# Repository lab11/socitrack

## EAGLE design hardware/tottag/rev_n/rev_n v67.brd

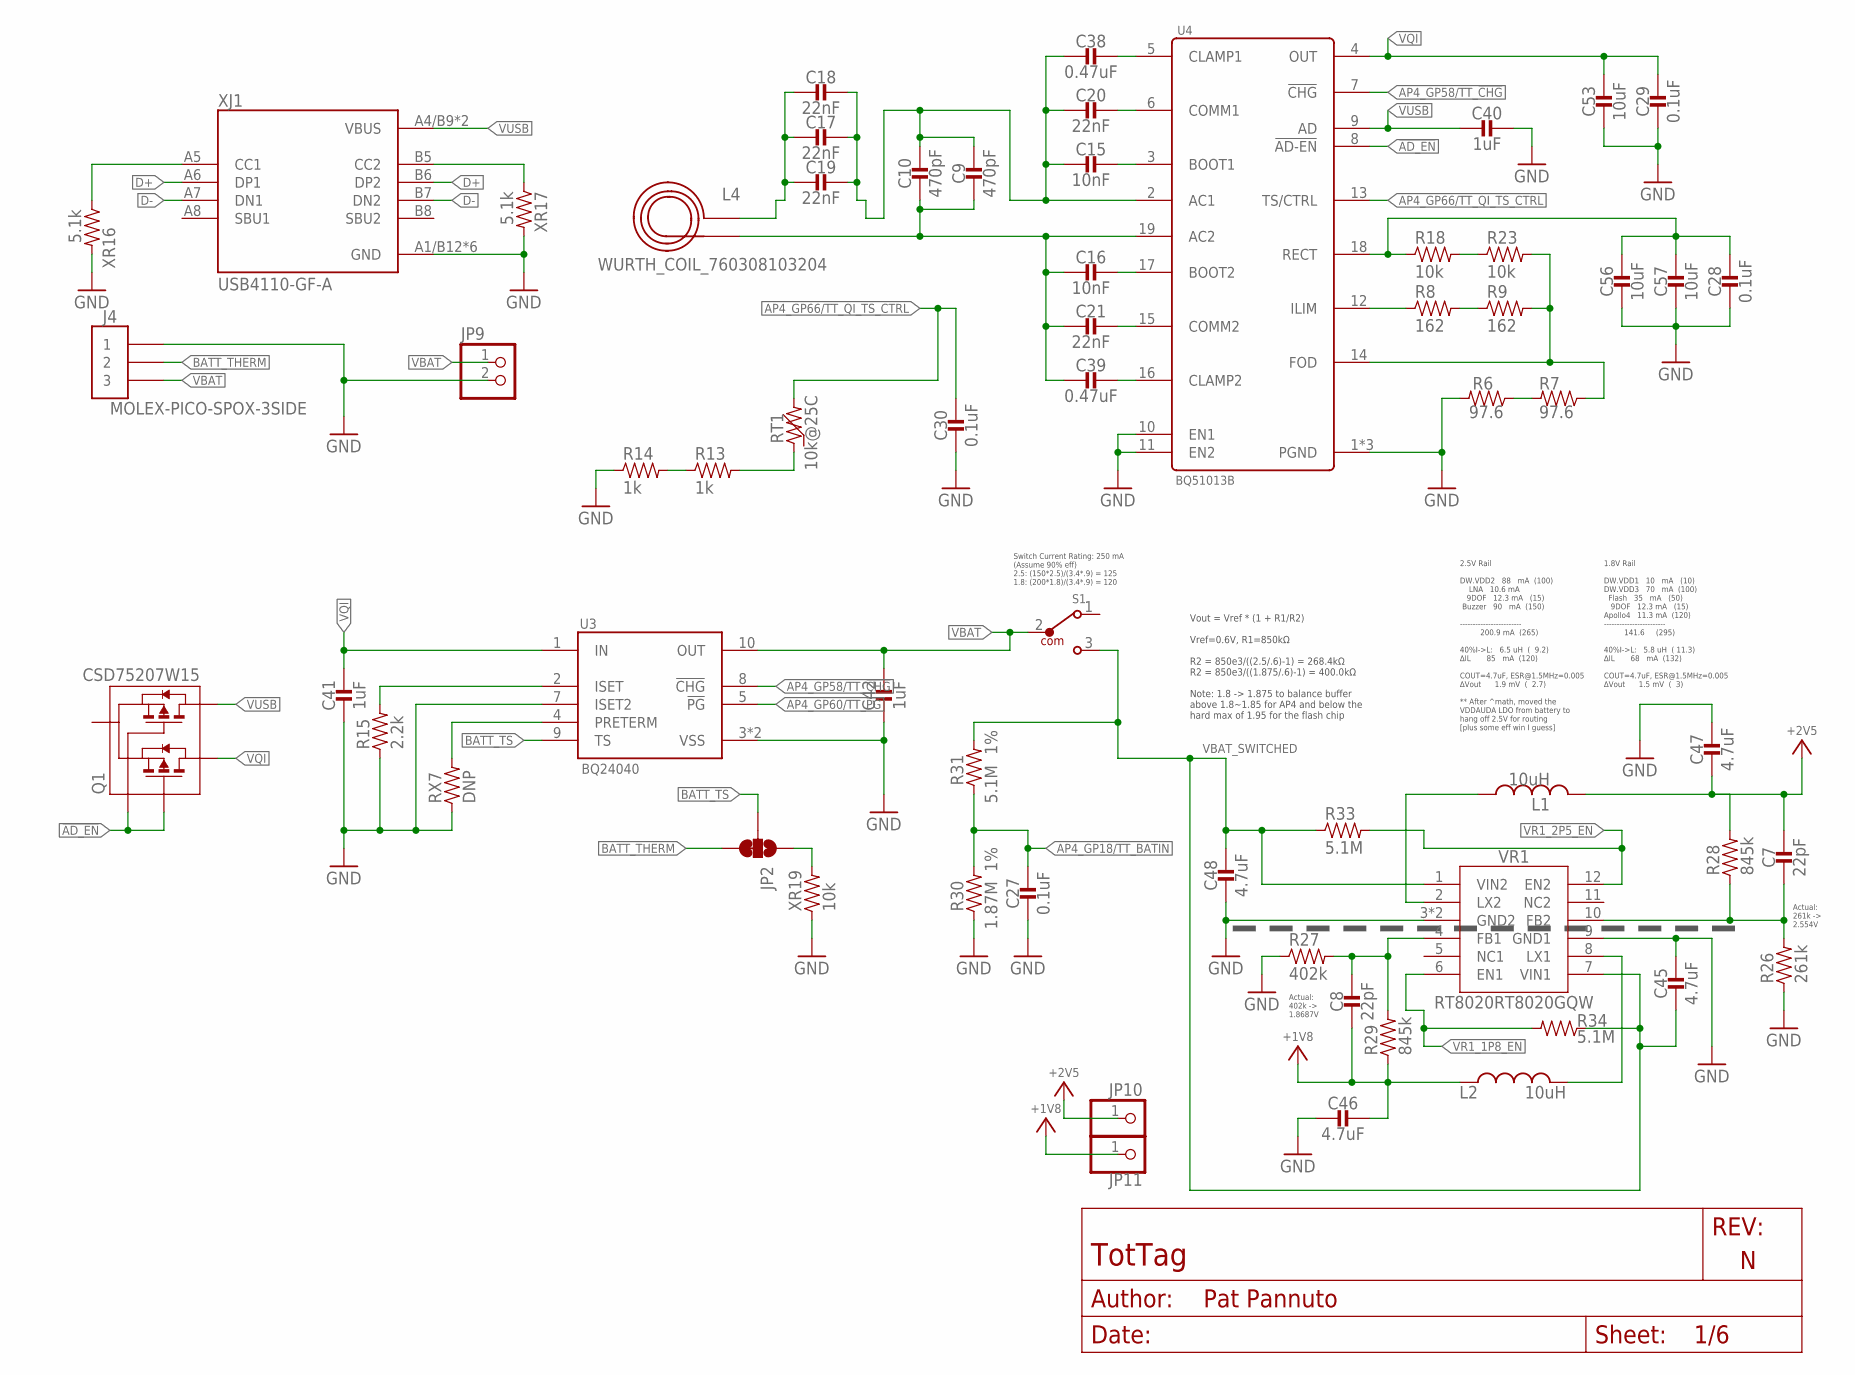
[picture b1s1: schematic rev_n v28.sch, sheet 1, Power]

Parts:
C7, C8: 22pF; 0201_CAP; MPN GRM0335C1H220FA01D
C9, C10: 470pF; 0402_CAP; MPN GRM1555C1H471JA01J; DIGIKEY 490-6242-1-ND
C15, C16: 10nF; 0402_CAP; MPN GRM155R71H103KA88J; DIGIKEY 490-6351-2-ND
C17, C18, C19: 22nF; 0402_CAP; MPN GRM155R71E223JA61D; DIGIKEY 490-10699-2-ND
C20, C21: 22nF; 0402_CAP; MPN CC0402ZRY5V8BB223; DIGIKEY 311-3823-1-ND
C27, C28, C29, C30: 0.1uF; 0402_CAP; MPN GRM155R71C104KA88J; DIGIKEY 490-6328-1-ND
C38, C39: 0.47uF; 0402_CAP; MPN GRT155R61E474ME01D; DIGIKEY 490-12270-1-ND
C40, C41, C42: 1uF; 0402_CAP; MPN GRM155R70J105KA12J
C45, C46, C47, C48: 4.7uF; 0603_CAP; MPN C1608X7S1A475K080AC
C53, C56, C57: 10uF; 0603_CAP; MPN CM105X5R106M25AT; DIGIKEY 1253-CM105X5R106M25ATCT-ND
J4: MOLEX-PICO-SPOX-3SIDE; MOLEX-PICO-SPOX-3_SIDE
JP2: JUMPER-SMT_3_1-NC_TRACE_SILK; SMT-JUMPER_3_1-NC_TRACE_SILK
JP9: PINHD-1X2; 1X02
JP10, JP11: PINHD-1X1; 1X01
L1, L2: 10uH; NRX3015; MPN NR3015T100M
L4: WURTH_COIL_760308103204
Q1: CSD75207W15; DSBGA
R6, R7: 97.6; 0402_RES; MPN RMCF0402FT97R6; DIGIKEY RMCF0402FT97R6CT-ND
R8, R9: 162; 0402_RES; MPN RMCF0402FT162R; DIGIKEY RMCF0402FT162RCT-ND
R13, R14: 1k; 0402_RES
R15: 2.2k; 0402_RES; MPN RMCF0402JT2K20; DIGIKEY RMCF0402JT2K20CT-ND
R18, R23: 10k; 0402_RES; MPN RC0402JR-0710KL; DIGIKEY 311-10KJRCT-ND
R26: 261k; 0201_RES; MPN ERJ-1GNF2613C
R27: 402k; 0201_RES; MPN ERJ-1GNF4023C
R28, R29: 845k; 0201_RES; MPN ERJ-1GNF8453C
R30: 1.87M; 0402_RES; TOLERANCE 1%; MPN RMCF0402FT1M87
R31: 5.1M; 0402_RES; TOLERANCE 1%; MPN RMCF0402FT5M10; DIGIKEY RMCF0402FT5M10CT-ND
R33, R34: 5.1M; 0402_RES; MPN RMCF0402FT5M10; DIGIKEY RMCF0402FT5M10CT-ND
RT1: 10k@25C; 0402_RES; MPN NCU15XH103F60RC; DIGIKEY 490-18149-1-ND
RX7: DNP; 0402_RES
S1: 450404015514; DIGIKEY 732-13665-1-ND
U3: BQ24040; DSQ0010A
U4: BQ51013B; RHL0020A
VR1: RT8020RT8020GQW; SON45P300X300X80-13T160X250N
XJ1: USB4110-GF-A; GCT_USB4110-GF-A
XR16, XR17: 5.1k; 0402_RES; MPN RMCF0402FT5K10; DIGIKEY RMCF0402FT5K10CT-ND
XR19: 10k; 0402_RES; MPN RC0402JR-0710KL; DIGIKEY 311-10KJRCT-ND

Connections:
!AD_EN: Q1.A1 (G1), Q1.C1 (G2), U4.8 (!AD-EN)
+2V5: C7.P$1 (1), C47.2, JP10.1, L1.P$2 (2), R28.2; also elsewhere on the board
AP4_GP18/TT_BATIN: C27.1, R30.2, R31.1; also elsewhere on the board
AP4_GP58/TT_!CHG: U3.8 (!CHG), U4.7 (!CHG); also elsewhere on the board
AP4_GP60/TT_!PG: U3.5 (!PG); also elsewhere on the board
AP4_GP66/TT_QI_TS_CTRL: C30.1, RT1.2, U4.13 (TS/CTRL); also elsewhere on the board
BATT_THERM: J4.2, J4.2SUPP (2), JP2.3; also elsewhere on the board
BATT_TS: JP2.2, U3.9 (TS); also elsewhere on the board
BQ_AC1: C9.1, C10.1, C15.2, C17.1, C18.1, C19.1, C20.2, C38.2, U4.2 (AC1)
BQ_AC2: C9.2, C10.2, C16.2, C21.2, C39.2, L4.P$2 (2), U4.19 (AC2)
BQ_BOOT1: C15.1, U4.3 (BOOT1)
BQ_BOOT2: C16.1, U4.17 (BOOT2)
BQ_CLAMP1: C38.1, U4.5 (CLAMP1)
BQ_CLAMP2: C39.1, U4.16 (CLAMP2)
BQ_COMM1: C20.1, U4.6 (COMM1)
BQ_COMM2: C21.1, U4.15 (COMM2)
BQ_FOD: R7.1, R9.2, R23.2, U4.14 (FOD)
BQ_ILM: R8.1, U4.12 (ILIM)
BQ_ISET: R15.2, U3.2 (ISET)
BQ_RECT: C28.1, C56.1, C57.1, R18.1, U4.18 (RECT)
COIL_AC1: C17.2, C18.2, C19.2, L4.P$1 (1)
D+: XJ1.A6 (DP1), XJ1.B6 (DP2)
D-: XJ1.A7 (DN1), XJ1.B7 (DN2)
GND: C27.2, C28.2, C29.2, C30.2, C40.1, C41.2, C42.2, C45.1, C46.2, C47.1, C48.2, C53.2, C56.2, C57.2, J4.1, J4.1SUPP (1), JP9.2, R6.2, R14.1, R15.1, R26.1, R27.1, R30.1, RX7.1, U3.3 (VSS), U3.7 (ISET2), U3.PAD (VSS), U4.1 (PGND), U4.10 (EN1), U4.11 (EN2), U4.20 (PGND), U4.PAD (PGND), VR1.3 (GND2), VR1.9 (GND1), VR1.13 (GND2), XJ1.A1/B12 (GND), XJ1.B1/A12 (GND), XJ1.S1 (GND), XJ1.S2 (GND), XJ1.S3 (GND), XJ1.S4 (GND), XR16.2, XR17.2, XR19.1; also elsewhere on the board
unnamed: R6.1, R7.2
unnamed 122: JP2.1, XR19.2; also elsewhere on the board
unnamed: RX7.2, U3.4 (PRETERM)
unnamed: R18.2, R23.1
unnamed: R8.2, R9.1
unnamed: R13.2, RT1.1
unnamed 127: R13.1, R14.2; also elsewhere on the board
VBAT: C42.1, J4.3, J4.3SUPP (3), JP9.1, S1.2, U3.10 (OUT); also elsewhere on the board
VBAT_SWITCHED: C45.2, C48.1, R31.2, R33.1, R34.1, S1.3, VR1.1 (VIN2), VR1.7 (VIN1)
VQI: C29.1, C41.1, C53.1, Q1.A2 (D1), Q1.A3 (D1), Q1.B3 (D1), U3.1 (IN), U4.4 (OUT)
VR1_1P8_EN: R34.2, VR1.6 (EN1)
VR1_2P5_EN: R33.2, VR1.12 (EN2)
VR1_FB1: C8.P$1 (1), R27.2, R29.2, VR1.4 (FB1)
VR1_FB2: C7.P$2 (2), R26.2, R28.1, VR1.10 (FB2)
VR1_LX1: L2.P$2 (2), VR1.8 (LX1)
VR1_LX2: L1.P$1 (1), VR1.2 (LX2)
VUSB: C40.2, Q1.B2 (D2), Q1.C2 (D2), Q1.C3 (D2), U4.9 (AD), XJ1.A4/B9 (VBUS), XJ1.B4/A9 (VBUS)

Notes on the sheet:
2.5V Rail DW.VDD2 88 mA (100) LNA 10.6 mA 9DOF 12.3 mA (15) Buzzer 90 mA (150) ------------------------ 200.9 mA (265) 40%I->L: 6.5 uH ( 9.2) ∆IL 85 mA (120) COUT=4.7uF, ESR@1.5MHz=0.005 ∆Vout 1.9 mV ( 2.7) ** After ^math, moved the VDDAUDA LDO from battery to hang off 2.5V for routing [plus some e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
1.8V Rail DW.VDD1 10 mA (10) DW.VDD3 70 mA (100) Flash 35 mA (50) 9DOF 12.3 mA (15) Apollo4 11.3 mA (120) ------------------------ 141.6 (295) 40%I->L: 5.8 uH ( 11.3) ∆IL 68 mA (132) COUT=4.7uF, ESR@1.5MHz=0.005 ∆Vout 1.5 mV ( 3)
Vout = Vref * (1 + R1/R2) Vref=0.6V, R1=850kΩ R2 = 850e3/((2.5/.6)-1) = 268.4kΩ R2 = 850e3/((1.875/.6)-1) = 400.0kΩ Note: 1.8 -> 1.875 to balance buffer above 1.8~1.85 for AP4 and below the hard max of 1.95 for the flash chip
Switch Current Rating: 250 mA (Assume 90% eff) 2.5: (150*2.5)/(3.4*.9) = 125 1.8: (200*1.8)/(3.4*.9) = 120
Actual: 402k -> 1.8687V
Actual: 261k -> 2.554V

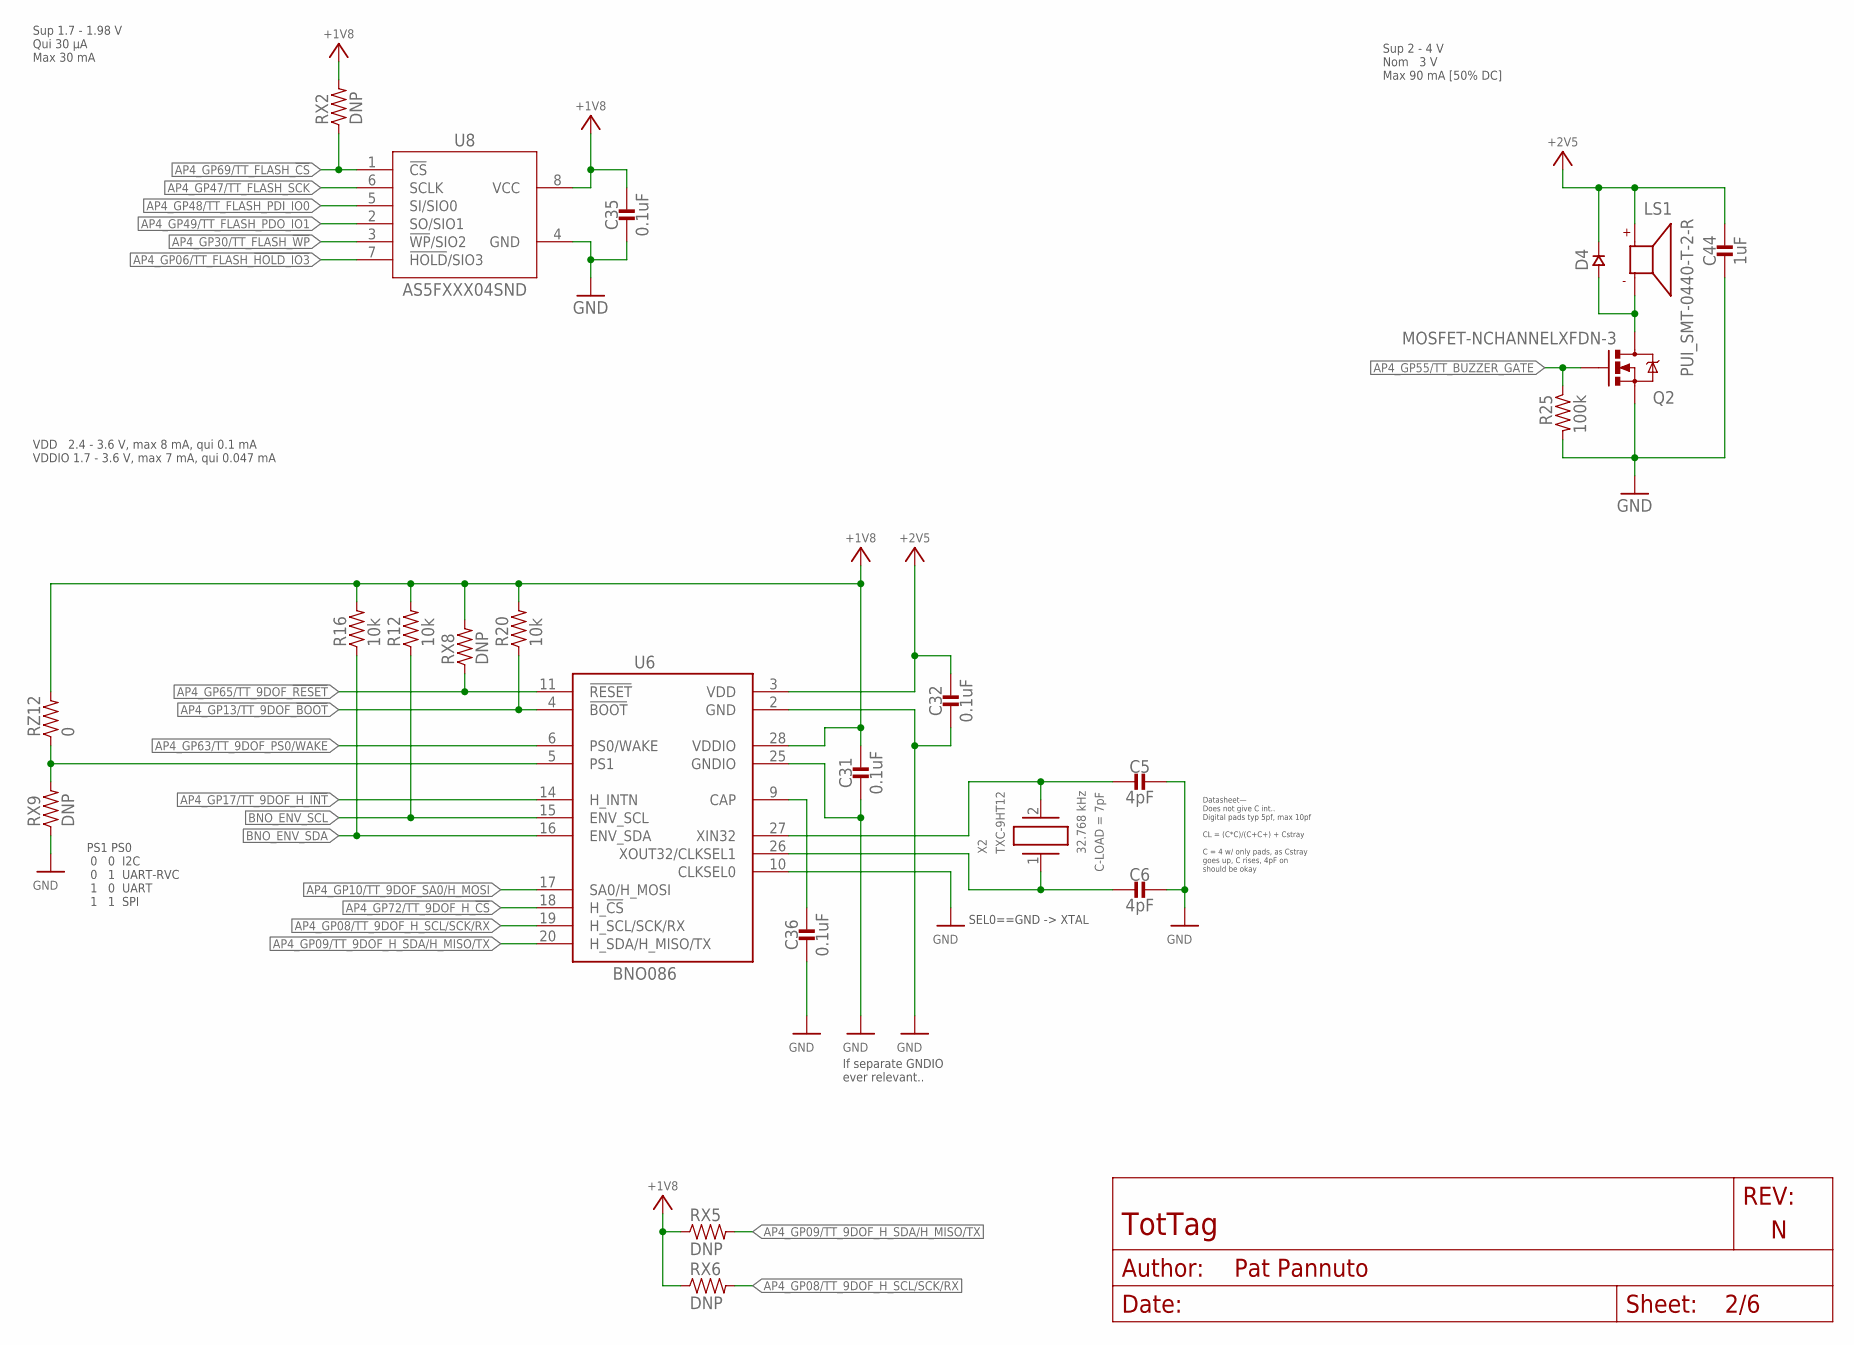
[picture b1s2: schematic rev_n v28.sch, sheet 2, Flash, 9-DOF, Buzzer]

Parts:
C5, C6: 4pF; 0201_CAP; MPN GRM0335C1H4R0BA01D
C31, C32, C35, C36: 0.1uF; 0402_CAP; MPN CL05A104KP5NNNC
C44: 1uF; 0402_CAP; MPN GRM155R70J105KA12J
D4: DIODE0402; 0402_DIODE; MPN CDSQR400B-HF; DIGIKEY 641-2087-1-ND
LS1: PUI_SMT-0440-T-2-R; SMT-0440-T-2-R
Q2: MOSFET-NCHANNELXFDN-3; XFDFN-3
R12, R16, R20: 10k; 0402_RES; MPN RC0402JR-0710KL; DIGIKEY 311-10KJRCT-ND
R25: 100k; 0402_RES; MPN RT0402BRE07100KL
RX2, RX5, RX6, RX8, RX9: DNP; 0603-RES
RZ12: 0; 0402_RES; MPN RMCF0402ZT0R00
U6: BNO086; LGA28R0P510X4_5P2X3P8X1
U8: AS5FXXX04SND; AS5FXXXXXXXX-XXLXN
X2: TXC-9HT12; MPN 9HT12-32.768KDZY-T

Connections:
9DOF_CAP: C36.1, U6.9 (CAP)
9DOF_XI: C5.P$2 (2), U6.27 (XIN32), X2.2
9DOF_XO: C6.P$2 (2), U6.26 (XOUT32/CLKSEL1), X2.1
+2V5: C32.1, C44.1, D4.CATHODE, LS1.+, U6.3 (VDD); also elsewhere on the board
AP4_GP06/TT_FLASH_!HOLD_IO3: U8.7 (!HOLD!/SIO3); also elsewhere on the board
AP4_GP08/TT_9DOF_H_SCL/SCK/RX: RX6.2, U6.19 (H_SCL/SCK/RX); also elsewhere on the board
AP4_GP13/TT_9DOF_!BOOT: R20.1, U6.4 (!BOOT); also elsewhere on the board
AP4_GP17/TT_9DOF_H_!INT: U6.14 (H_INTN); also elsewhere on the board
AP4_GP30/TT_FLASH_!WP: U8.3 (!WP!/SIO2); also elsewhere on the board
AP4_GP47/TT_FLASH_SCK: U8.6 (SCLK); also elsewhere on the board
AP4_GP48/TT_FLASH_PDI_IO0: U8.5 (SI/SIO0); also elsewhere on the board
AP4_GP49/TT_FLASH_PDO_IO1: U8.2 (SO/SIO1); also elsewhere on the board
AP4_GP55/TT_BUZZER_GATE: Q2.G, R25.1; also elsewhere on the board
AP4_GP63/TT_9DOF_PS0/WAKE: U6.6 (PS0/WAKE); also elsewhere on the board
AP4_GP65/TT_9DOF_!RESET: RX8.1, U6.11 (!RESET); also elsewhere on the board
AP4_GP69/TT_FLASH_!CS: RX2.1, U8.1 (!CS); also elsewhere on the board
AP4_GP72/TT_9DOF_H_!CS: U6.18 (H_!CS); also elsewhere on the board
BNO_ENV_SCL: R12.1, U6.15 (ENV_SCL)
BNO_ENV_SDA: R16.1, U6.16 (ENV_SDA)
BNO_PS1: RX9.2, RZ12.1, U6.5 (PS1); also elsewhere on the board
GND: C5.P$1 (1), C6.P$1 (1), C31.2, C32.2, C35.2, C36.2, C44.2, Q2.S, R25.2, RX9.1, U6.2 (GND), U6.10 (CLKSEL0), U6.25 (GNDIO), U8.4 (GND); also elsewhere on the board
unnamed: D4.ANODE, LS1.- (N), Q2.D

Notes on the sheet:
Sup 1.7 - 1.98 V Qui 30 µA Max 30 mA
VDD 2.4 - 3.6 V, max 8 mA, qui 0.1 mA VDDIO 1.7 - 3.6 V, max 7 mA, qui 0.047 mA
Sup 2 - 4 V Nom 3 V Max 90 mA [50% DC]
If separate GNDIO ever relevant..
Datasheet— Does not give C int.. Digital pads typ 5pf, max 10pf CL = (C*C)/(C+C+) + Cstray C = 4 w/ only pads, as Cstray goes up, C rises, 4pF on should be okay
SEL0==GND -> XTAL
PS1 PS0 0 0 I2C 0 1 UART-RVC 1 0 UART 1 1 SPI

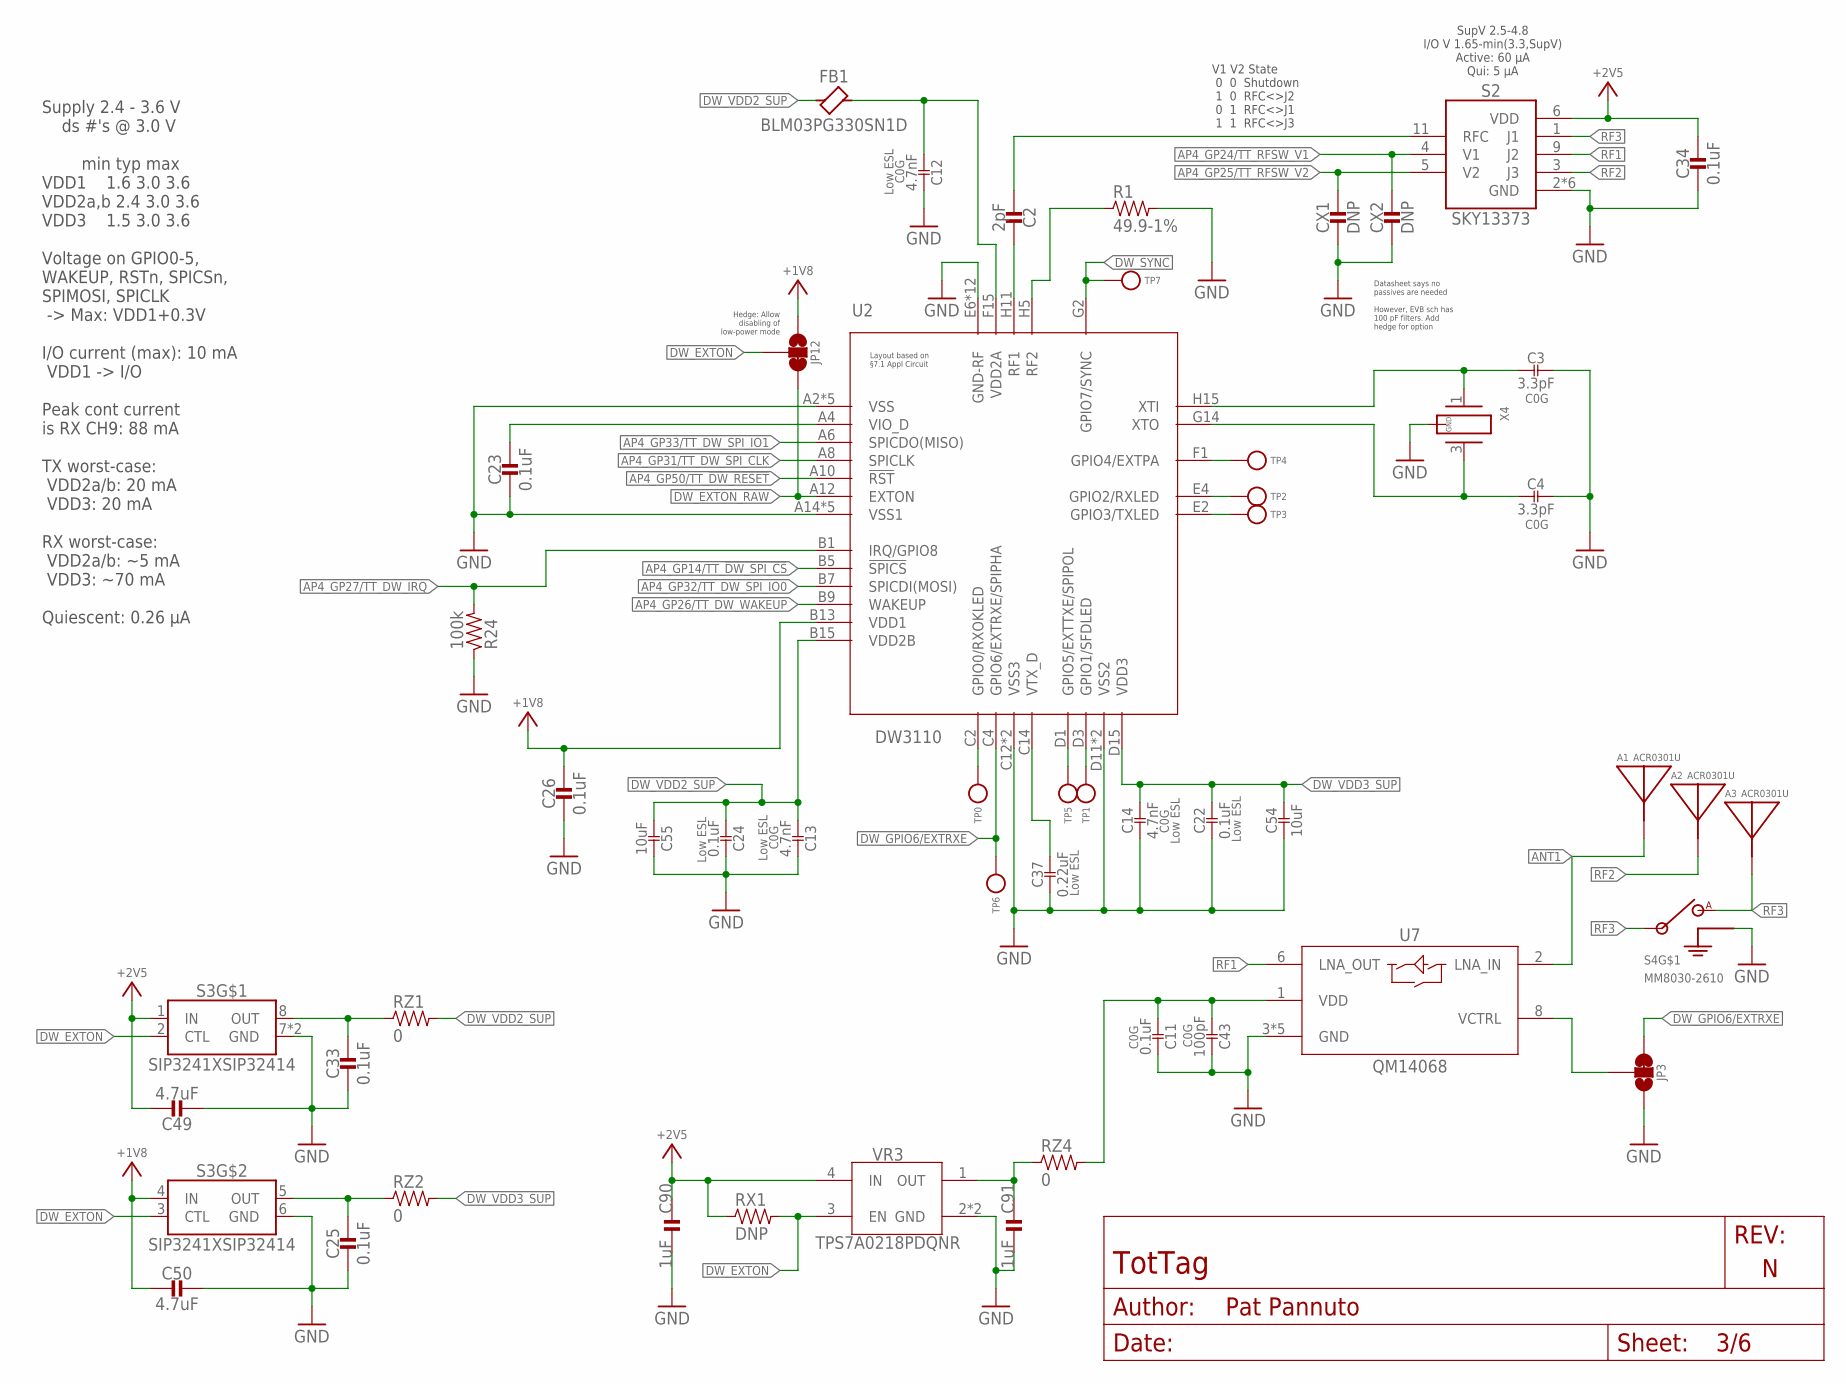
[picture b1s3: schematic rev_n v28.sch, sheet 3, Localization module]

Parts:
A1, A2, A3: ACR0301U
C2: 2pF; 0201_CAP; MPN CBR02C209A5GAC
C3, C4: 3.3pF; SMD_2012M-0805US-C; MPN 600F3R3BT250XT
C11: 0.1uF; SMD_3216M-1206US-C; MPN GRM31C5C1H104JA01L
C12, C13, C14: 4.7nF; SMD_1608M-0603US-C; MPN C0603C472J5GAC7867
C22, C24: 0.1uF; SMD_1608M-0603US-C; MPN C1608X7R1H104K080AA
C23, C25, C26, C33, C34: 0.1uF; 0402_CAP; MPN CL05A104KP5NNNC
C37: 0.22uF; SMD_1608M-0603US-C; MPN C1608X7R1H224K080AB
C43: 100pF; SMD_1005M-0402US-C; MPN C0402C101J3GACTU
C49, C50: 4.7uF; 0603_CAP; MPN C1608X7S1A475K080AC
C54, C55: 10uF; SMD_1608M-0603US-C; MPN CM105X5R106M25AT
C90, C91: 1uF; 0201_CAP; MPN GRM033R61A105ME44D
CX1, CX2: DNP; 0603_CAP
FB1: BLM03PG330SN1D; 0201_FB; MPN BLM03PG330SN1D
JP3, JP12: JUMPER-SMT_3_1-NC_TRACE_SILK; SMT-JUMPER_3_1-NC_TRACE_SILK
R1: 49.9-1%; 0201_RES; MPN ERJ-1GNF49R9C
R24: 100k; 0402_RES; MPN RT0402BRE07100KL
RX1: DNP; 0603-RES
RZ1, RZ2: 0; 0603-RES; MPN RMCF0603ZT0R00
RZ4: 0; 0402_RES; MPN RMCF0402ZT0R00
S2: SKY13373
S3: SIP3241XSIP32414; TDFN2X2X0P6-8
S4: MM8030-2610
TP0, TP1, TP2, TP3, TP4, TP5, TP6, TP7: TEST-POINT; PAD.03X.03
U2: DW3110; WLCSP52
U7: QM14068
VR3: TPS7A0218PDQNR; 4-XDFN-EP
X4: TXC-8Y

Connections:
+2V5: C34.1, C49.1, C90.P$1 (1), RX1.1, S2.6 (VDD), S3.1 (IN), VR3.4 (IN); also elsewhere on the board
ANT1: A1.FEED, U7.2 (LNA_IN)
AP4_GP14/TT_!DW_SPI_CS: U2.B5 (!SPICS); also elsewhere on the board
AP4_GP24/TT_RFSW_V1: CX2.1, S2.4 (V1); also elsewhere on the board
AP4_GP25/TT_RFSW_V2: CX1.1, S2.5 (V2); also elsewhere on the board
AP4_GP26/TT_DW_WAKEUP: U2.B9 (WAKEUP); also elsewhere on the board
AP4_GP27/TT_DW_IRQ: R24.2, U2.B1 (IRQ/GPIO8); also elsewhere on the board
AP4_GP31/TT_DW_SPI_CLK: U2.A8 (SPICLK); also elsewhere on the board
AP4_GP32/TT_DW_SPI_IO0: U2.B7 (SPICDI(MOSI)); also elsewhere on the board
AP4_GP33/TT_DW_SPI_IO1: U2.A6 (SPICDO(MISO)); also elsewhere on the board
AP4_GP50/TT_!DW_RESET: U2.A10 (!RST); also elsewhere on the board
DW_EXTON: JP12.2, RX1.2, S3.2 (CTL), S3.3 (CTL), VR3.3 (EN); also elsewhere on the board
DW_EXTON_RAW: JP12.3, U2.A12 (EXTON); also elsewhere on the board
DW_GPIO4: TP4.P$1, U2.F1 (GPIO4/EXTPA)
DW_GPIO5: TP5.P$1, U2.D1 (GPIO5/EXTTXE/SPIPOL)
DW_GPIO6/EXTRXE: JP3.3, TP6.P$1, U2.C4 (GPIO6/EXTRXE/SPIPHA); also elsewhere on the board
DW_RF1: C2.P$1 (1), U2.H11 (RF1)
DW_RF2: R1.1, U2.H5 (RF2)
DW_RXLED: TP2.P$1, U2.E4 (GPIO2/RXLED)
DW_RXOKLED: TP0.P$1, U2.C2 (GPIO0/RXOKLED)
DW_SFDLED: TP1.P$1, U2.D3 (GPIO1/SFDLED)
DW_SYNC: TP7.P$1, U2.G2 (GPIO7/SYNC)
DW_TXLED: TP3.P$1, U2.E2 (GPIO3/TXLED)
DW_VDD2A: C12.P$1, FB1.P$2, U2.F15 (VDD2A)
DW_VDD2_PWROUT: C33.1, RZ1.1, S3.8 (OUT)
DW_VDD2_SUP: C13.P$1, C24.P$1, C55.P$1, FB1.P$1, RZ1.2, U2.B15 (VDD2B)
DW_VDD3_PWROUT: C25.1, RZ2.1, S3.5 (OUT)
DW_VDD3_SUP: C14.P$2, C22.P$2, C54.P$2, RZ2.2, U2.D15 (VDD3)
DW_VIO_D: C23.1, U2.A4 (VIO_D)
DW_VTX_D: C37.P$2, U2.C14 (VTX_D)
DW_XT0: C4.P$1, U2.G14 (XTO), X4.3 (2)
DW_XTI: C3.P$1, U2.H15 (XTI), X4.1
GND: C3.P$2, C4.P$2, C11.P$2, C12.P$2, C13.P$2, C14.P$1, C22.P$1, C23.2, C24.P$2, C25.2, C26.2, C33.2, C34.2, C37.P$1, C43.P$2, C49.2, C50.1, C54.P$1, C55.P$2, C90.P$2 (2), C91.P$2 (2), CX1.2, CX2.2, JP3.1, R1.2, R24.1, S2.2 (GND), S2.7 (GND), S2.8 (GND), S2.10 (GND), S2.12 (GND), S2.PAD (GND), S3.6 (GND), S3.7 (GND), S3.PAD (GND), S4.G1 (GND), S4.G2 (GND), U2.A2 (VSS), U2.A14 (VSS1), U2.B3 (VSS), U2.B11 (VSS1), U2.C6 (VSS), U2.C8 (VSS1), U2.C10 (VSS1), U2.C12 (VSS3), U2.D5 (VSS), U2.D7 (VSS), U2.D9 (VSS1), U2.D11 (VSS2), U2.D13 (VSS3), U2.E6 (GND-RF), U2.E10 (GND-RF), U2.E12 (GND-RF), U2.E14 (VSS2), U2.F7 (GND-RF), U2.F9 (GND-RF), U2.G6 (GND-RF), U2.G10 (GND-RF), U2.H1 (GND-RF), U2.H3 (GND-RF), U2.H7 (GND-RF), U2.H9 (GND-RF), U2.H13 (GND-RF), U7.3 (GND), U7.4 (GND), U7.5 (GND), U7.7 (GND), U7.9 (GND), VR3.2 (GND), VR3.PAD (GND), X4.2 (GND), X4.4 (GND); also elsewhere on the board
LNA_VCTRL: JP3.2, U7.8 (VCTRL); also elsewhere on the board
RF1: S2.9 (J2), U7.6 (LNA_OUT)
RF2: A2.FEED, S2.3 (J3)
RF3: A3.FEED, S2.1 (J1), S4.IN, S4.OUT (A)
RFC: C2.P$2 (2), S2.11 (RFC)
VDD_LNA: C11.P$1, C43.P$1, RZ4.2, U7.1 (VDD)
VR3_OUT: C91.P$1 (1), RZ4.1, VR3.1 (OUT)

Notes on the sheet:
Supply 2.4 - 3.6 V ds #'s @ 3.0 V min typ max VDD1 1.6 3.0 3.6 VDD2a,b 2.4 3.0 3.6 VDD3 1.5 3.0 3.6 Voltage on GPIO0-5, WAKEUP, RSTn, SPICSn, SPIMOSI, SPICLK -> Max: VDD1+0.3V I/O current (max): 10 mA VDD1 -> I/O Peak cont current is RX CH9: 88 mA TX worst-case: VDD2a/b: 20 mA VDD3: 20 mA RX worst-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
SupV 2.5-4.8 I/O V 1.65-min(3.3,SupV) Active: 60 µA Qui: 5 µA
V1 V2 State 0 0 Shutdown 1 0 RFC<>J2 0 1 RFC<>J1 1 1 RFC<>J3
Datasheet says no passives are needed However, EVB sch has 100 pF filters. Add hedge for option
Hedge: Allow disabling of low-power mode

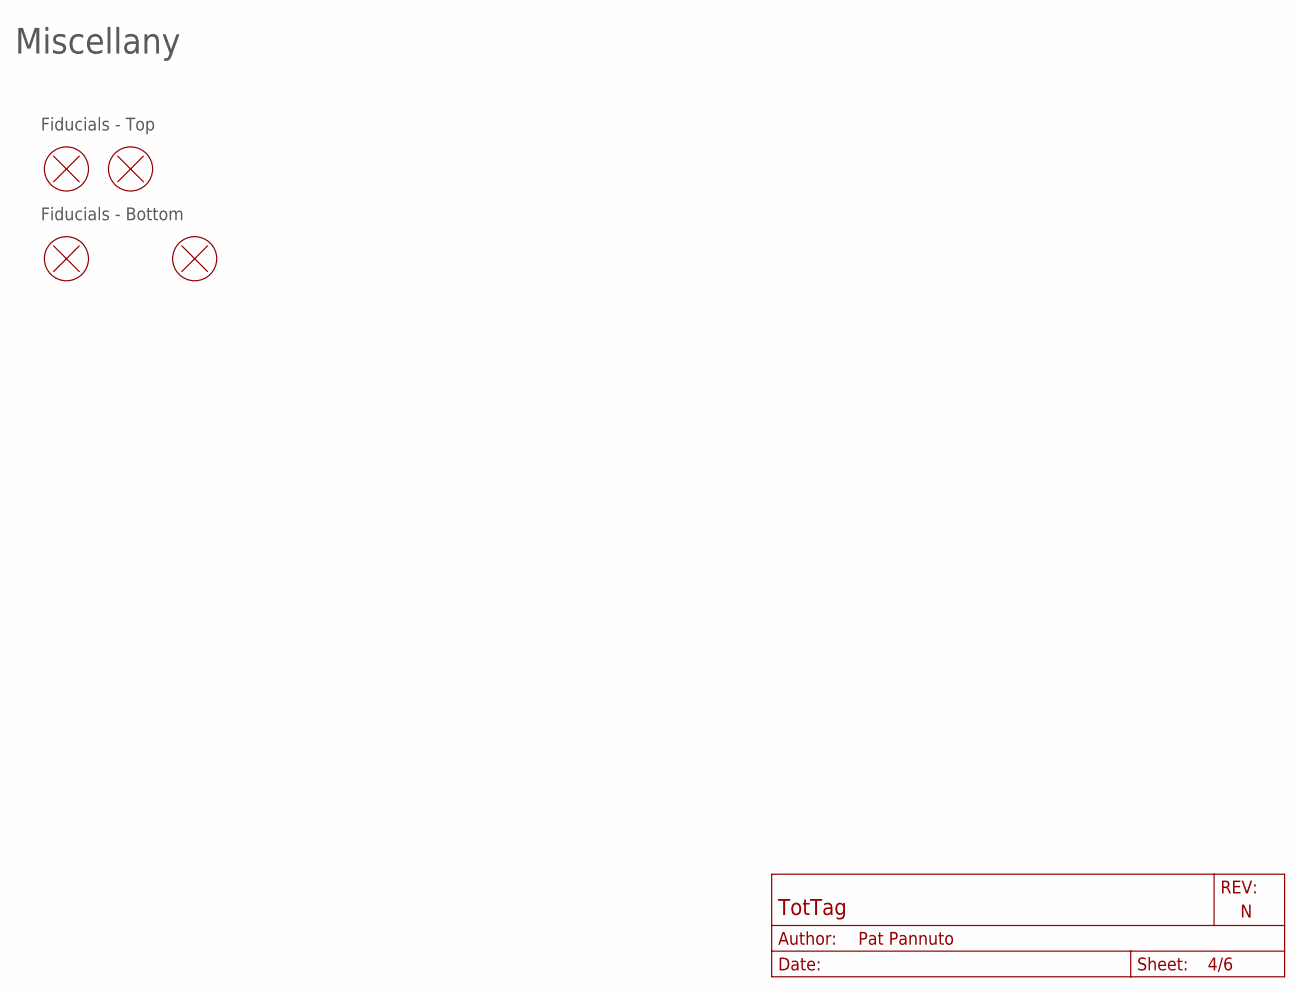
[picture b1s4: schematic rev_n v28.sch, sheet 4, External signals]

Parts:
FD1, FD2, FD4, FD6: FIDUCIAL; FIDUCIAL_1MM-CU_2MM-MASK

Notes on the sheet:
Miscellany
Fiducials - Top
Fiducials - Bottom

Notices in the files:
parts and their libraries:
Wurth_Switch_WS-SLSU: Copyright: Würth Elektronik
SparkFun-Jumpers: Licensing: Creative Commons ShareAlike 4.0 International - https://creativecommons.org/licenses/by-sa/4.0
